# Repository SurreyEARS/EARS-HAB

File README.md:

# EARS-HAB
EARS High Altitude Balloon Project

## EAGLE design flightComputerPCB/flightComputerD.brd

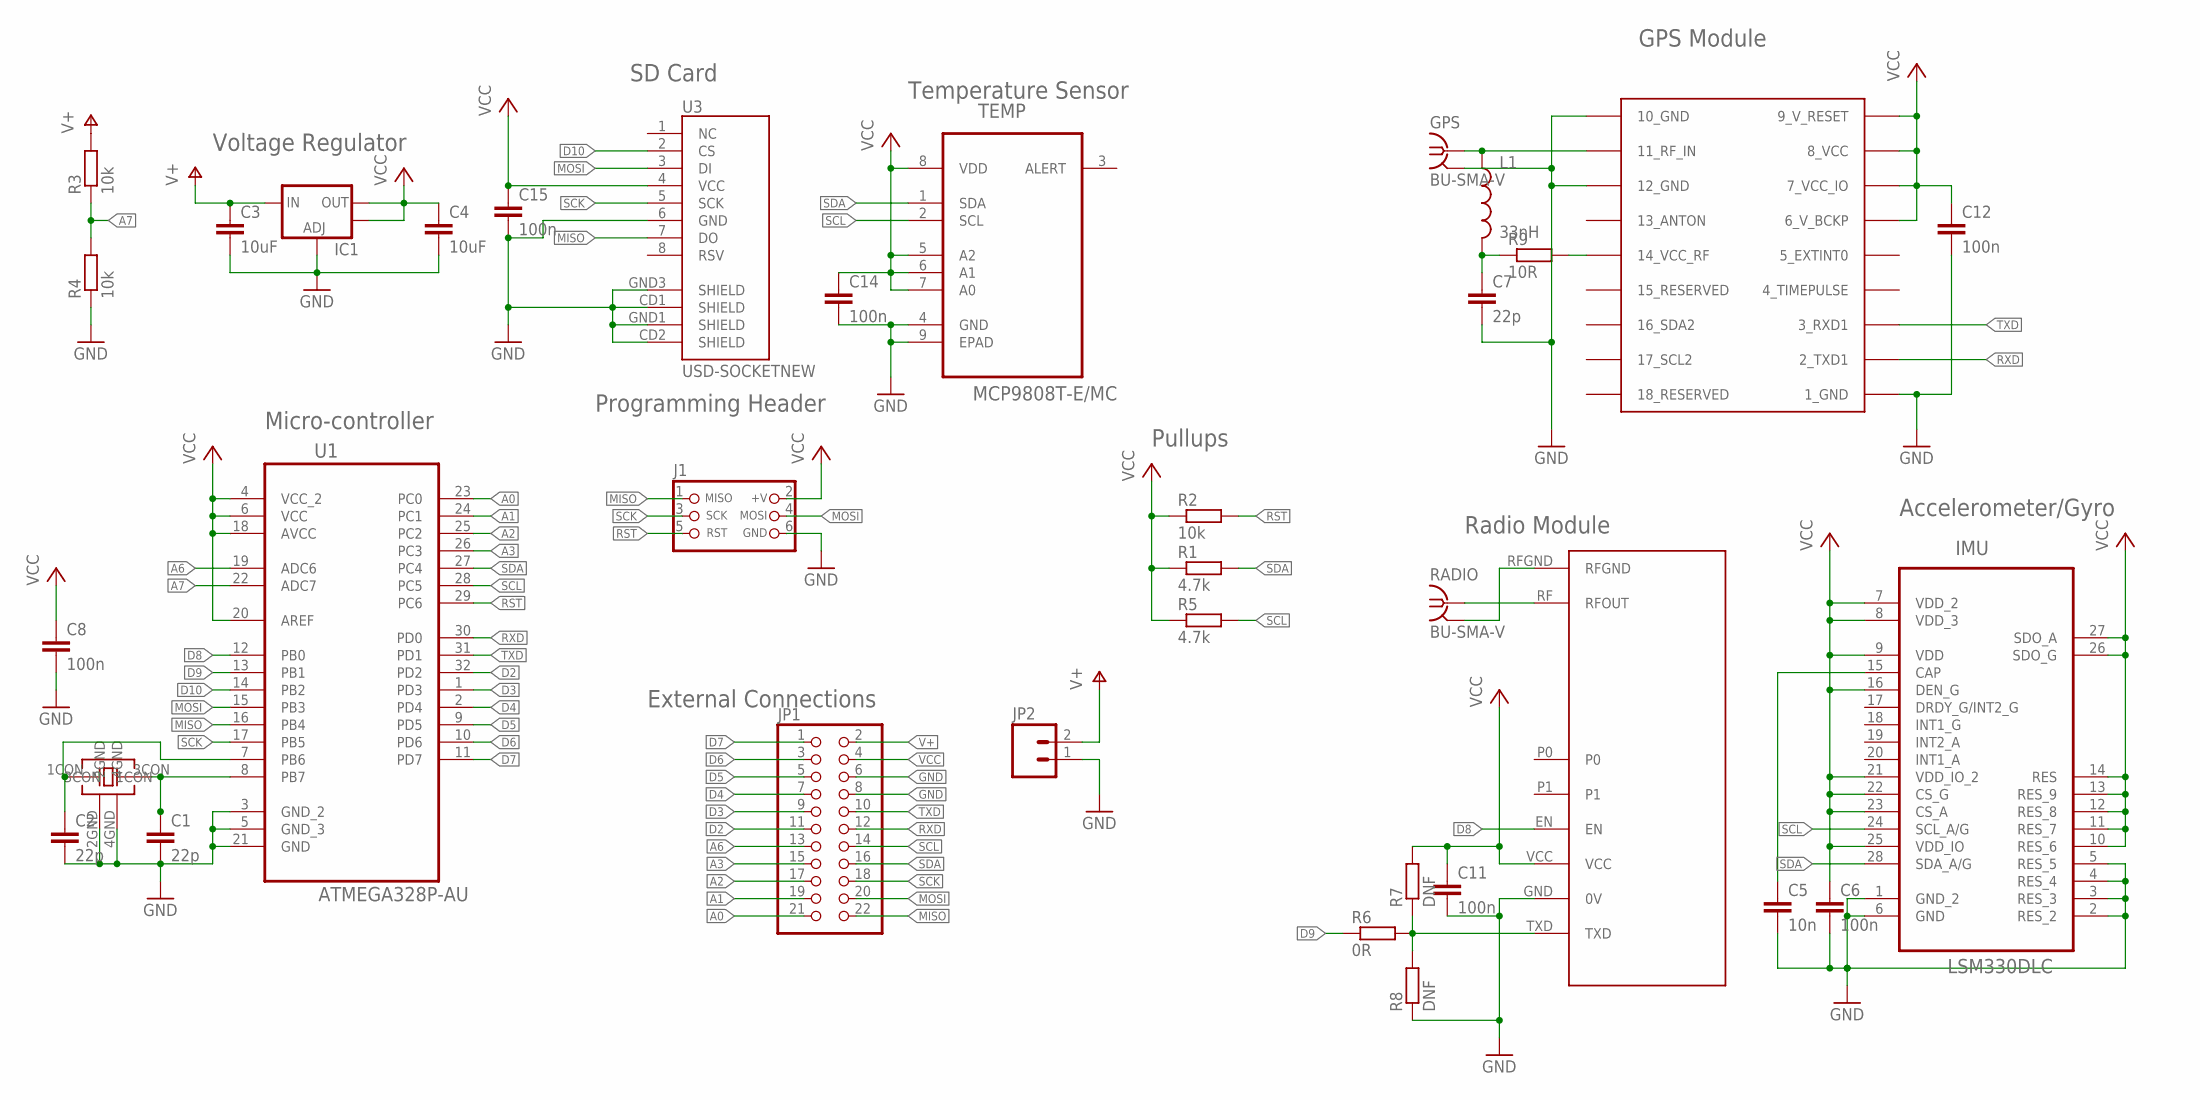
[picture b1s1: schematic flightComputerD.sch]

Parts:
C1, C2, C7: 22p; C0603
C3, C4: 10uF; C0603
C5: 10n; C0603
C6, C8, C11, C12, C14, C15: 100n; C0603
GPS: BU-SMA-V
IC1: V_REG_LM1117SOT223; SOT223
IMU: LSM330DLC; LGA28R50P6X8_400X500X110
J1: CON_HEADER_PRG_AVR_ICSP-PTH; HEADER_PRG_2X03
JP1: PINHD-2X11; 2X11
JP2: M02PTH; 1X02
L1: 33nH; 0603
R1, R5: 4.7k; R0603
R2, R3, R4: 10k; R0603
R6: 0R; R0603
R7, R8: DNF; R0603
R9: 10R; R0603
RADIO: BU-SMA-V
TEMP: MCP9808T-E/MC; DFN300X200X100-9N
U1: ATMEGA328P-AU; QFP80P900X900X120-32N
U3: USD-SOCKETNEW; MICRO-SD-SOCKET-PP
U$1: CRYSTAL
U$4: UBLOX_MAX
U$6: RADIOMETRIX-MTX2

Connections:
A0: JP1.21, U1.23 (PC0)
A1: JP1.19, U1.24 (PC1)
A2: JP1.17, U1.25 (PC2)
A3: JP1.15, U1.26 (PC3)
A6: JP1.13, U1.19 (ADC6)
A7: R3.1, R4.2, U1.22 (ADC7)
D2: JP1.11, U1.32 (PD2)
D3: JP1.9, U1.1 (PD3)
D4: JP1.7, U1.2 (PD4)
D5: JP1.5, U1.9 (PD5)
D6: JP1.3, U1.10 (PD6)
D7: JP1.1, U1.11 (PD7)
D8: U1.12 (PB0), U$6.EN
D9: R6.1, U1.13 (PB1)
D10: U1.14 (PB2), U3.2 (CS)
GND: C1.2, C2.2, C3.2, C4.2, C5.2, C6.2, C7.2, C8.2, C11.2, C12.2, C14.2, C15.2, GPS.2, GPS.3 (2), GPS.4 (2), GPS.5 (2), IC1.1 (ADJ), IMU.1 (GND_2), IMU.2 (RES_2), IMU.3 (RES_3), IMU.4 (RES_4), IMU.5 (RES_5), IMU.6 (GND), J1.6 (GND), JP1.6, JP1.8, JP2.1, R4.1, R8.1, TEMP.4 (GND), TEMP.9 (EPAD), U1.3 (GND_2), U1.5 (GND_3), U1.21 (GND), U3.6 (GND), U3.CD1 (SHIELD), U3.CD2 (SHIELD), U3.GND1 (SHIELD), U3.GND3 (SHIELD), U$1.2GND, U$1.4GND, U$4.1_GND, U$4.10_GND, U$4.12_GND, U$6.GND (0V)
MISO: J1.1 (MISO), JP1.22, U1.16 (PB4), U3.7 (DO)
MOSI: J1.4 (MOSI), JP1.20, U1.15 (PB3), U3.3 (DI)
unnamed: GPS.1, L1.1, U$4.11_RF_IN
unnamed: C1.1, U1.8 (PB7), U$1.3CON
unnamed: R9.2, U$4.14_VCC_RF
unnamed: C2.1, U1.7 (PB6), U$1.1CON
unnamed: RADIO.1, U$6.RF (RFOUT)
unnamed: R6.2, R7.1, R8.2, U$6.TXD
unnamed: C7.1, L1.2, R9.1
unnamed: C5.1, IMU.15 (CAP)
RFGND: RADIO.2, RADIO.3 (2), RADIO.4 (2), RADIO.5 (2), U$6.RFGND
RST: J1.5 (RST), R2.2, U1.29 (PC6)
RXD: JP1.12, U1.30 (PD0), U$4.2_TXD1
SCK: J1.3 (SCK), JP1.18, U1.17 (PB5), U3.5 (SCK)
SCL: IMU.24 (SCL_A/G), JP1.14, R5.2, TEMP.2 (SCL), U1.28 (PC5)
SDA: IMU.28 (SDA_A/G), JP1.16, R1.2, TEMP.1 (SDA), U1.27 (PC4)
TXD: JP1.10, U1.31 (PD1), U$4.3_RXD1
V+: C3.1, IC1.3 (IN), JP1.2, JP2.2, R3.2
VCC: C4.1, C6.1, C8.1, C11.1, C12.1, C14.1, C15.1, IC1.2 (OUT), IC1.4 (OUT), IMU.7 (VDD_2), IMU.8 (VDD_3), IMU.9 (VDD), IMU.10 (RES_6), IMU.11 (RES_7), IMU.12 (RES_8), IMU.13 (RES_9), IMU.14 (RES), IMU.16 (DEN_G), IMU.21 (VDD_IO_2), IMU.22 (CS_G), IMU.23 (CS_A), IMU.25 (VDD_IO), IMU.26 (SDO_G), IMU.27 (SDO_A), J1.2 (+V), JP1.4, R1.1, R2.1, R5.1, R7.2, TEMP.5 (A2), TEMP.6 (A1), TEMP.7 (A0), TEMP.8 (VDD), U1.4 (VCC_2), U1.6 (VCC), U1.18 (AVCC), U1.20 (AREF), U3.4 (VCC), U$4.6_V_BCKP, U$4.7_VCC_IO, U$4.8_VCC, U$4.9_V_RESET, U$6.VCC

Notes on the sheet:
Micro-controller
Temperature Sensor
Voltage Regulator
Radio Module
GPS Module
SD Card
Programming Header
Accelerometer/Gyro
Pullups
External Connections

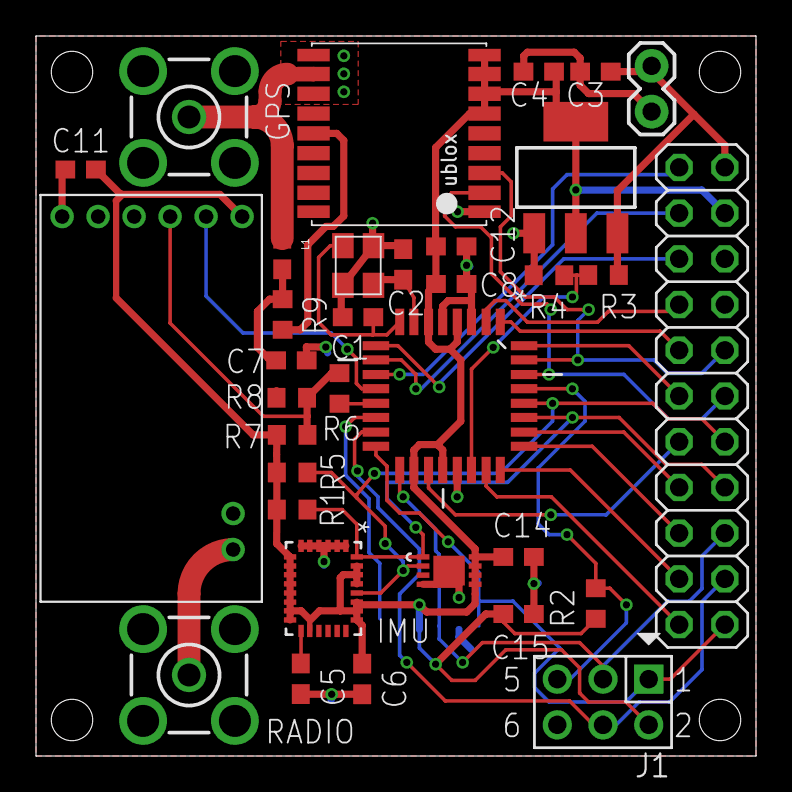
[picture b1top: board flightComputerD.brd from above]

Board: 2 copper layers, 40.0 x 40.0 mm, 35 parts (1 on the bottom side), 35 nets.

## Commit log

2015-04-07 Restructured

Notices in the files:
parts and their libraries:
SparkFun: Licensing: CC v3.0 Share-Alike You are welcome to use this library for commercial purposes.
